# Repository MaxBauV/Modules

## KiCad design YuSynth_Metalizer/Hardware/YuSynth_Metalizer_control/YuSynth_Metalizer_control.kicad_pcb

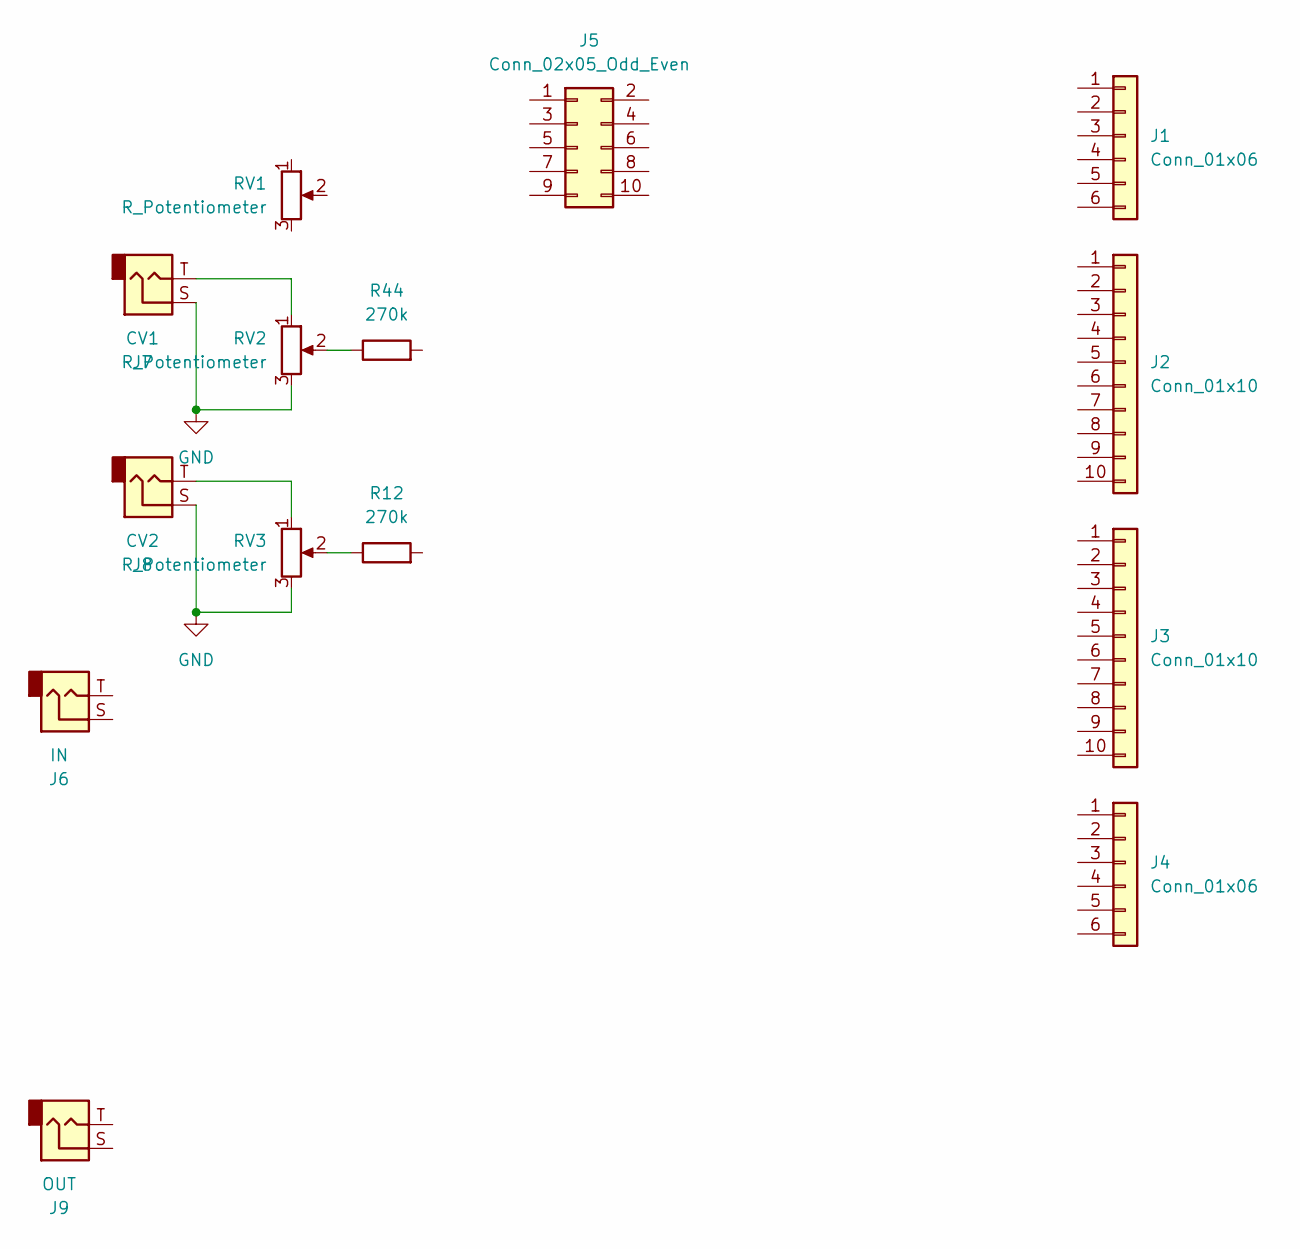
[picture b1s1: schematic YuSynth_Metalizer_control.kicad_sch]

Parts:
J1, J4: Conn_01x06; PinHeader_1x06_P2.54mm_Vertical
J2, J3: Conn_01x10; PinHeader_1x10_P2.54mm_Vertical
J5: Conn_02x05_Odd_Even; IDC-Header_2x05_P2.54mm_Vertical
J6: IN; Jack_3.5mm_QingPu_WQP-PJ398SM_Vertical
J7: CV1; Jack_3.5mm_QingPu_WQP-PJ398SM_Vertical
J8: CV2; Jack_3.5mm_QingPu_WQP-PJ398SM_Vertical
J9: OUT; Jack_3.5mm_QingPu_WQP-PJ398SM_Vertical
R12, R44: 270k; R_Axial_DIN0204_L3.6mm_D1.6mm_P7.62mm_Horizontal
RV1, RV2, RV3: R_Potentiometer; Potentiometer_Alpha_RD901F-40-00D_Single_Vertical

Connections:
GND: J7.S, J8.S, RV2.3, RV3.3
unnamed: J7.T, RV2.1
unnamed: J8.T, RV3.1
unnamed: R12.1, RV3.2
unnamed: R44.1, RV2.2

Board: 2 copper layers, 14 parts (5 on the bottom side), 5 nets, no tracks yet.

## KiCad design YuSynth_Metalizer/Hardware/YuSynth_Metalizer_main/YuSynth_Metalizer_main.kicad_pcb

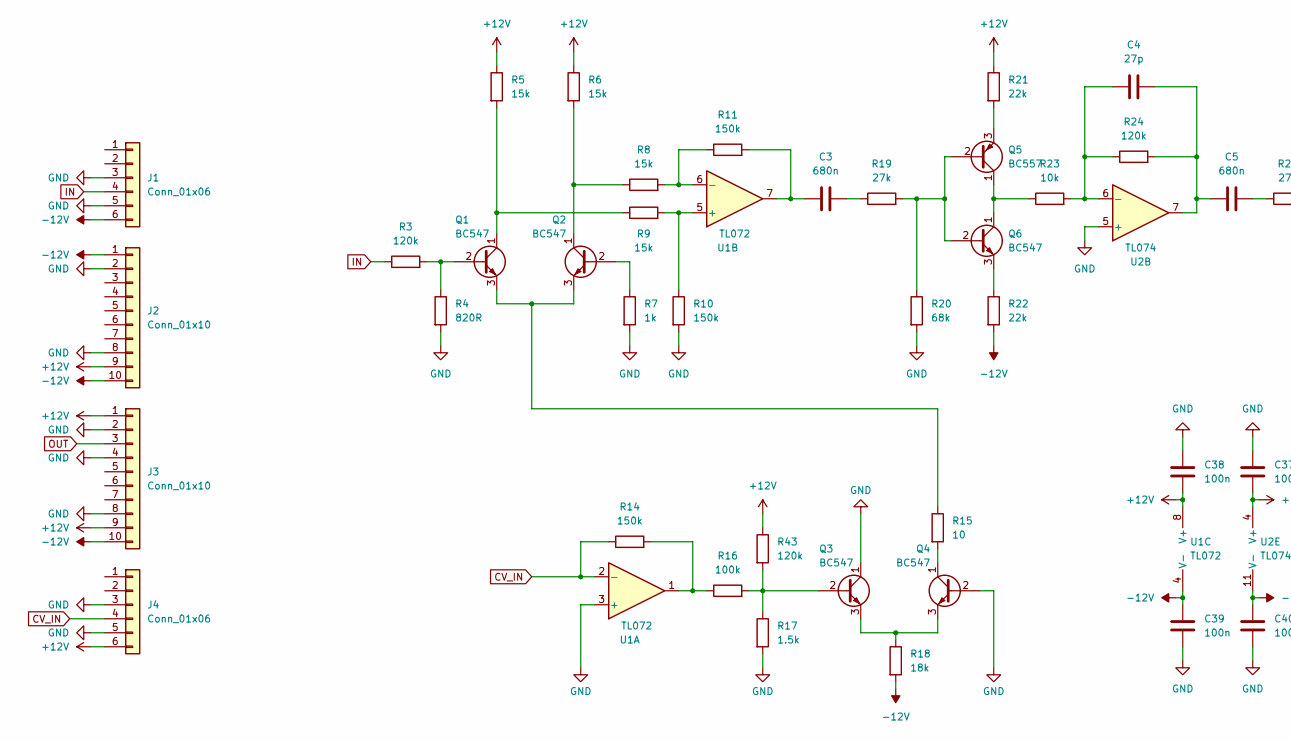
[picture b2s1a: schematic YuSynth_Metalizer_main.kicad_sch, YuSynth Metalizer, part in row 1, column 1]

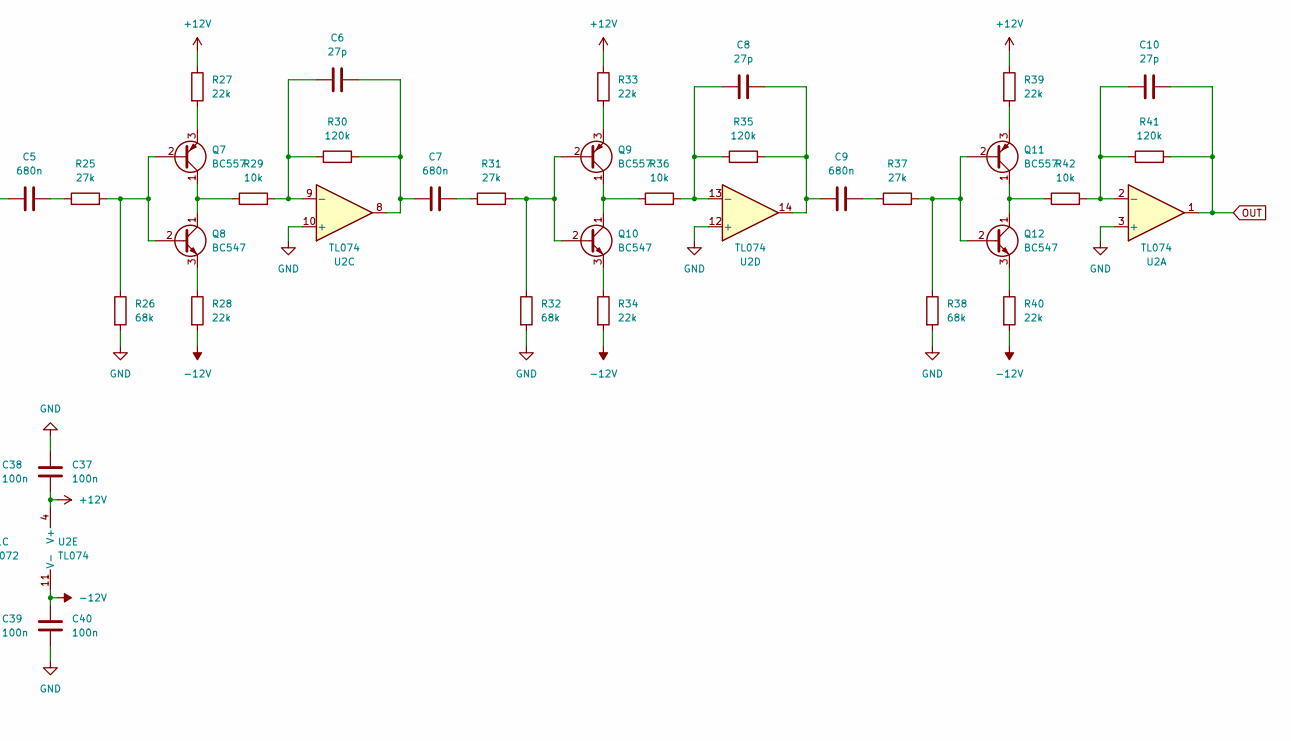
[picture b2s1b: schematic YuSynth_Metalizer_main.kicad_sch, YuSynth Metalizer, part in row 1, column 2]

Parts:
C3, C5, C7, C9: 680n; C_Rect_L7.0mm_W3.5mm_P5.00mm
C4, C6, C8, C10: 27p; C_Rect_L4.0mm_W2.5mm_P2.50mm
C37, C38, C39, C40: 100n; C_Rect_L4.6mm_W2.0mm_P2.50mm_MKS02_FKP02
J1, J4: Conn_01x06; PinSocket_1x06_P2.54mm_Vertical
J2, J3: Conn_01x10; PinSocket_1x10_P2.54mm_Vertical
Q1, Q2, Q3, Q4, Q6, Q8, Q10, Q12: BC547; TO-92_Inline
Q5, Q7, Q9, Q11: BC557; TO-92_Inline
R3, R24, R30, R35, R41, R43: 120k; R_Axial_DIN0204_L3.6mm_D1.6mm_P7.62mm_Horizontal
R4: 820R; R_Axial_DIN0204_L3.6mm_D1.6mm_P7.62mm_Horizontal
R5, R6, R8, R9: 15k; R_Axial_DIN0204_L3.6mm_D1.6mm_P7.62mm_Horizontal
R7: 1k; R_Axial_DIN0204_L3.6mm_D1.6mm_P7.62mm_Horizontal
R10, R11, R14: 150k; R_Axial_DIN0204_L3.6mm_D1.6mm_P7.62mm_Horizontal
R15: 10; R_Axial_DIN0204_L3.6mm_D1.6mm_P7.62mm_Horizontal
R16: 100k; R_Axial_DIN0204_L3.6mm_D1.6mm_P7.62mm_Horizontal
R17: 1.5k; R_Axial_DIN0204_L3.6mm_D1.6mm_P7.62mm_Horizontal
R18: 18k; R_Axial_DIN0204_L3.6mm_D1.6mm_P7.62mm_Horizontal
R19, R25, R31, R37: 27k; R_Axial_DIN0204_L3.6mm_D1.6mm_P7.62mm_Horizontal
R20, R26, R32, R38: 68k; R_Axial_DIN0204_L3.6mm_D1.6mm_P7.62mm_Horizontal
R21, R22, R27, R28, R33, R34, R39, R40: 22k; R_Axial_DIN0204_L3.6mm_D1.6mm_P7.62mm_Horizontal
R23, R29, R36, R42: 10k; R_Axial_DIN0204_L3.6mm_D1.6mm_P7.62mm_Horizontal
U1: TL072; DIP-8_W7.62mm_LongPads
U2: TL074; DIP-14_W7.62mm_LongPads

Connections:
+12V: C37.2, C38.2, J2.9, J3.1, J3.9, J4.6, R5.1, R6.1, R21.1, R27.1, R33.1, R39.1, R43.1, U1.8 (V+), U2.4 (V+)
-12V: C39.1, C40.1, J1.6, J2.1, J2.10, J3.10, R18.2, R22.2, R28.2, R34.2, R40.2, U1.4 (V-), U2.11 (V-)
CV_IN: J4.4, R14.1, U1.2 (-)
GND: C37.1, C38.1, C39.2, C40.2, J1.3, J1.5, J2.2, J2.8, J3.2, J3.4, J3.8, J4.3, J4.5, Q3.1 (C), Q4.2 (B), R4.2, R7.2, R10.2, R17.2, R20.2, R26.2, R32.2, R38.2, U1.3 (+), U2.3 (+), U2.5 (+), U2.10 (+), U2.12 (+)
IN: J1.4, R3.1
unnamed: C3.1, R11.2, U1.7
unnamed: C3.2, R19.1
unnamed: C4.2, C5.1, R24.2, U2.7
unnamed: C5.2, R25.1
unnamed: C6.2, C7.1, R30.2, U2.8
unnamed: C7.2, R31.1
unnamed: C8.2, C9.1, R35.2, U2.14
unnamed: C9.2, R37.1
unnamed: Q1.2 (B), R3.2, R4.1
unnamed: Q1.1 (C), R5.2, R9.1
unnamed: Q1.3 (E), Q2.3 (E), R15.1
unnamed: Q2.2 (B), R7.1
unnamed: Q2.1 (C), R6.2, R8.1
unnamed: Q3.2 (B), R16.2, R17.1, R43.2
unnamed: Q3.3 (E), Q4.3 (E), R18.1
unnamed: Q4.1 (C), R15.2
unnamed: Q5.2 (B), Q6.2 (B), R19.2, R20.1
unnamed: Q5.1 (C), Q6.1 (C), R23.1
unnamed: Q5.3 (E), R21.2
unnamed: Q6.3 (E), R22.1
unnamed: Q7.2 (B), Q8.2 (B), R25.2, R26.1
unnamed: Q7.1 (C), Q8.1 (C), R29.1
unnamed: Q7.3 (E), R27.2
unnamed: Q8.3 (E), R28.1
unnamed: Q9.3 (E), R33.2
unnamed: Q9.2 (B), Q10.2 (B), R31.2, R32.1
unnamed: Q9.1 (C), Q10.1 (C), R36.1
unnamed: Q10.3 (E), R34.1
unnamed: Q11.2 (B), Q12.2 (B), R37.2, R38.1
unnamed: Q11.1 (C), Q12.1 (C), R42.1
unnamed: Q11.3 (E), R39.2
unnamed: Q12.3 (E), R40.1
unnamed: R14.2, R16.1, U1.1
unnamed: R9.2, R10.1, U1.5 (+)
unnamed: R8.2, R11.1, U1.6 (-)
unnamed: C10.1, R41.1, R42.2, U2.2 (-)
unnamed: C4.1, R23.2, R24.1, U2.6 (-)
unnamed: C6.1, R29.2, R30.1, U2.9 (-)
unnamed: C8.1, R35.1, R36.2, U2.13 (-)
OUT: C10.2, J3.3, R41.2, U2.1

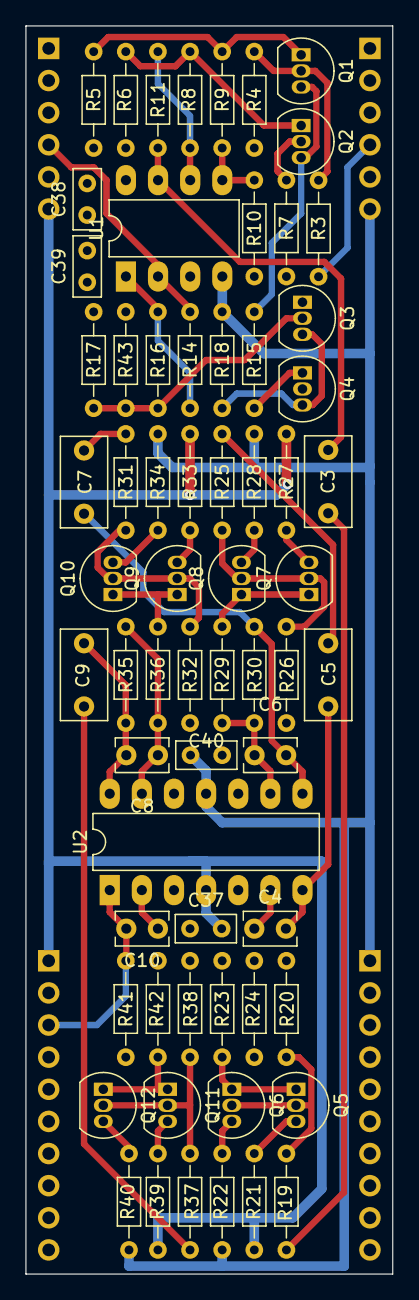
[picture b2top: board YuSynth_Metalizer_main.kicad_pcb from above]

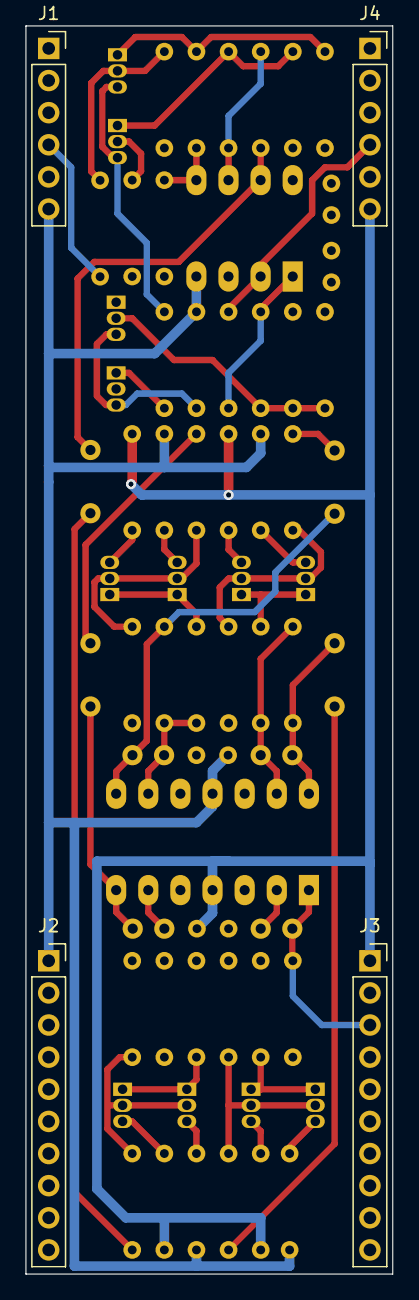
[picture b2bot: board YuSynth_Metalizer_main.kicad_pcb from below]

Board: 2 copper layers, 29.0 x 98.7 mm, 69 parts (4 on the bottom side), 45 nets.

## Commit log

2024-02-08 Added undone YuSynth Metalizer
2024-02-08 Done with YuSynth Metalizer schematic, starting with 6hp THT PCB
2024-02-08 Added .DS_Store to .gitignore
2024-02-08 Fixed OpAmp supply range error & redid PCB
2024-02-10 Main board & panel nearly done
2024-02-10 Finished panel & redid file structure
2024-02-11 Redid all boards
2024-02-11 Added Xor-tillator schematic
2024-02-12 Continued with XOR-tillator
2024-02-15 continued XOR-tillator
